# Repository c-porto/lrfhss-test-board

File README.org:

#+HTML: <div align="center">

#+HTML: 
#+HTML: 

* LR-FHSS Test Board 

#+HTML:   </a>
#+HTML:   
#+HTML:   
#+HTML:   
#+HTML:   
#+HTML:   
#+HTML:   <a href="https://doi.org/10.5281/zenodo.19164080"></br>

A simple PCB for testing the LR-FHSS

[[#overview][Overview]] • [[#repository-organization][Repository Organization]] • [[#license][License]] • [[#releases][Releases]] • [[#notes][Notes]] • [[#references][References]]

#+HTML: </div>

* Overview
:PROPERTIES:
:CUSTOM_ID: overview
:END:

The PCB... was based on the on the NiceRF (LoRa1262F30) module...

* Repository Organization
:PROPERTIES:
:CUSTOM_ID: repository-organization
:END:

#+begin_src text  
  lrfhss-test-board/
    ├── README.org
    ├── sources/
    └── outputs/
#+end_src

- =sources/= :: Main files of the... hardware project.
- =outputs/= :: Output files, such as figures of the...PCB, schematics, BOM and more.

* License
:PROPERTIES:
:CUSTOM_ID: license
:END:

This project is open-source under the following license: CERN Open Hardware License v2.0.

* Releases
:PROPERTIES:
:CUSTOM_ID: releases
:END:

Releases are published after ensuring that the project itself does not have any major errors and after testing the PCB. Please refer to the *documentation* for more details.

* Notes
:PROPERTIES:
:CUSTOM_ID: notes
:END:

For more info about the ...

* References
:PROPERTIES:
:CUSTOM_ID: references
:END:

# - <<ref1>> [1] D. L. Figueiredo, "Reliability Enhanced Electrical Power System for Nanosatellites," in /Repositório Institucional da UFSC/, pp. 1-85, 2023, available at [[https://repositorio.ufsc.br/bitstream/handle/123456789/247559/PEEL2103-D.pdf?sequence=1&isAllowed=y][this link]].

# - <<ref2>> [2] C. A. Rigo, L. O. Seman, M. D. Berejuck and E. A. Bezerra, "Printed Circuit Board Design Methodology for Embedded Systems Targeting Space Applications," in /IEEE Latin America Transactions/, vol. 18, no. 02, pp. 257-264, 2020, available at [[https://ieeexplore.ieee.org/document/9085278][this link]].

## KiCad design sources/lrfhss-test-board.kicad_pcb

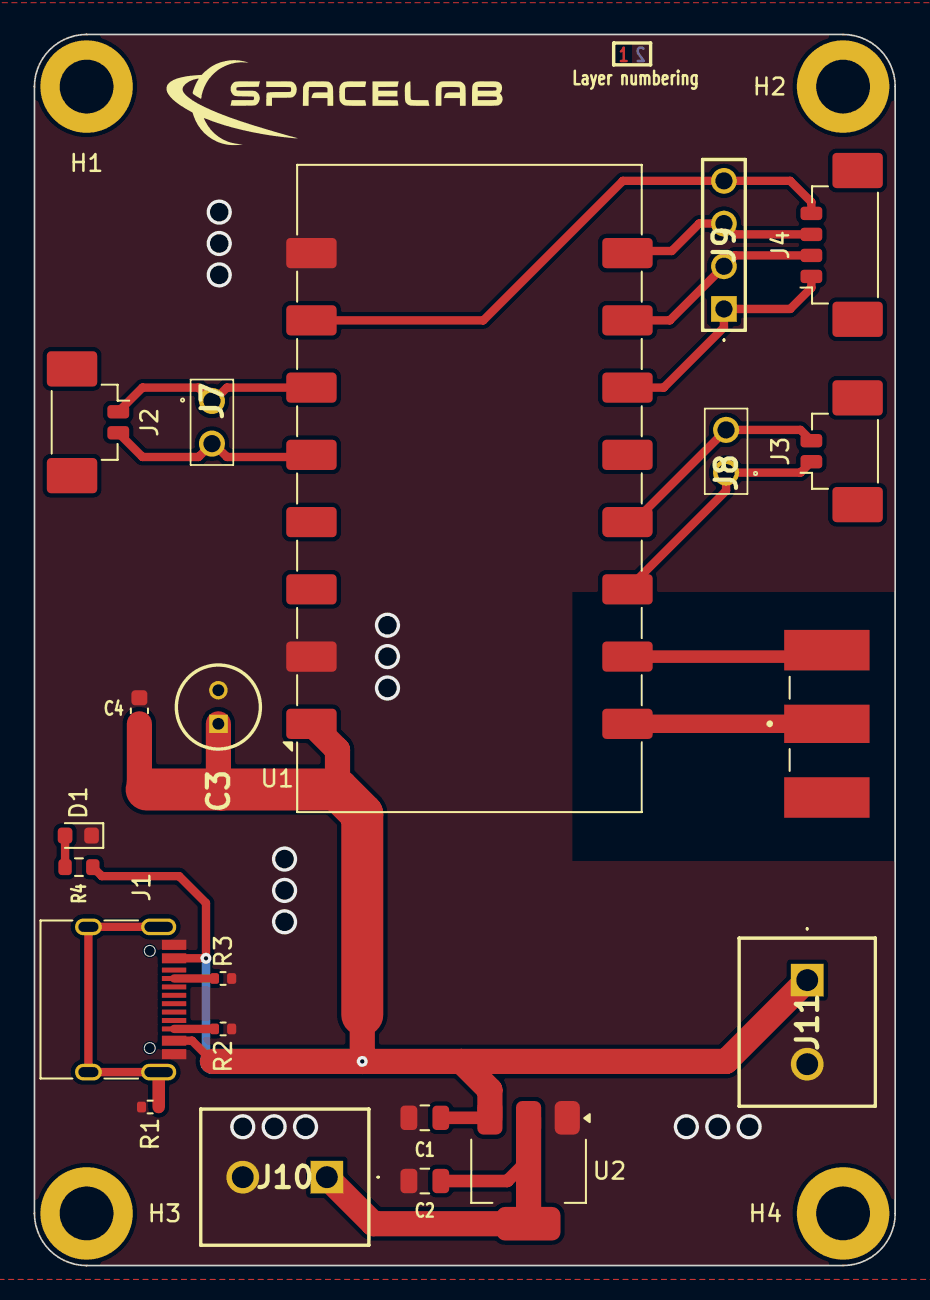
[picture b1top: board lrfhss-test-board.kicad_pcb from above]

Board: 2 copper layers, 51.2 x 73.2 mm, 25 parts (0 on the bottom side), 17 nets.

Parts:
C1, C2: 1uF; CAP0805
C3: 47uF; CAP47UELECTROLYTIC
C4: 100nF; CAP0603
D1: LED; LED_0603_1608Metric
H1, H2, H3, H4: Mounting hole (3.2 mm); MountingHole
J1: USB-C; GENERIC-USB-C
J2, J3: 532610271
J4: 532610471
J5: 142-0701-801
J7, J8: Conn_01x02_Pin; TSW-102-07-G-S
J9: Conn_01x04_Pin; TSW-104-07-G-S
J10, J11: Screw_Terminal_01x02; MV-152
R1: 1M; RES0402
R2, R3: 5.11k; RES0402
R4: 1k; RES0603
U1: LoRa126XF30
U2: AMS1117-3.3; SOT-223-3_TabPin2

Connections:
3V3: C2.2, J10.1, U2.2 (VO)
/CTRL0: J2.2, J7.2, U1.5 (~RESET)
/CTRL1: J2.1, J7.1, U1.6 (BUSY)
/DATA0: J3.1, J8.1, U1.14 (DIO3)
/DATA1: J3.2, J8.2, U1.13 (DIO1)
/SPI0: J4.1, J9.1, U1.11 (MOSI)
/SPI1: J4.2, J9.2, U1.10 (MISO)
/SPI2: J4.3, J9.3, U1.9 (SCK)
/SPI3: J4.4, J9.4, U1.7 (~NSS)
ANT: J5.1, U1.16 (ANT)
GND: C1.1, C2.1, C3.2, C4.1, D1.1 (K), J1.A1 (GND), J1.A12 (GND), J1.B1 (GND), J1.B12 (GND), J10.2, J11.2, R1.1, R2.1, R3.1, U1.2 (GND), U1.8 (GND), U2.1 (GND)
GND1: J5.S1, J5.S2, J5.S3, J5.S4, U1.15 (GND)
unnamed: D1.2 (A), R4.1
unnamed: J1.A5 (CC1), R3.2
unnamed: J1.B5 (CC2), R2.2
unnamed: J1.S1 (SHIELD), R1.2
VBUS: C1.2, C3.1, C4.2, J1.A4 (VBUS), J1.A9 (VBUS), J1.B4 (VBUS), J1.B9 (VBUS), J11.1, R4.2, U1.1 (VCC), U2.3 (VI)

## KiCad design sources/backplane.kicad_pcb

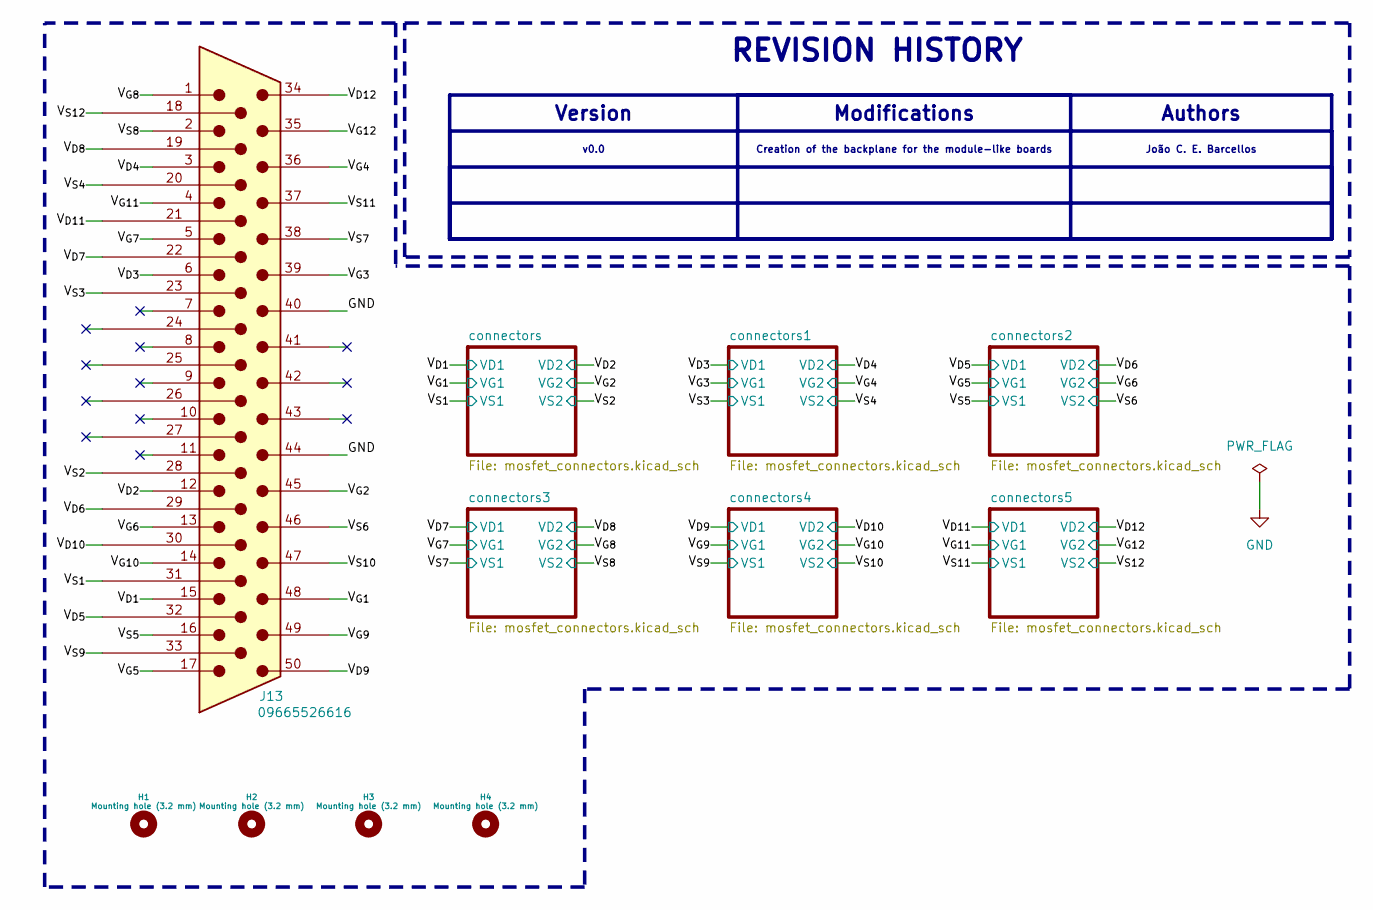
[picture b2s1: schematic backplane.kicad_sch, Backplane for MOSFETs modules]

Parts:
H1, H2, H3, H4: Mounting hole (3.2 mm); MountingHole; MPN N/A
J13: 09665526616; 966552616; Manufacturer_Part_Number 09665526616; Mouser Part Number 617-09-66-552-6616

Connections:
/V_{D1}: J13.15; also elsewhere on the board
/V_{D2}: J13.12; also elsewhere on the board
/V_{D3}: J13.6; also elsewhere on the board
/V_{D4}: J13.3; also elsewhere on the board
/V_{D5}: J13.32; also elsewhere on the board
/V_{D6}: J13.29; also elsewhere on the board
/V_{D7}: J13.22; also elsewhere on the board
/V_{D8}: J13.19; also elsewhere on the board
/V_{D9}: J13.50; also elsewhere on the board
/V_{D10}: J13.30; also elsewhere on the board
/V_{D11}: J13.21; also elsewhere on the board
/V_{D12}: J13.34; also elsewhere on the board
/V_{G1}: J13.48; also elsewhere on the board
/V_{G2}: J13.45; also elsewhere on the board
/V_{G3}: J13.39; also elsewhere on the board
/V_{G4}: J13.36; also elsewhere on the board
/V_{G5}: J13.17; also elsewhere on the board
/V_{G6}: J13.13; also elsewhere on the board
/V_{G7}: J13.5; also elsewhere on the board
/V_{G8}: J13.1; also elsewhere on the board
/V_{G9}: J13.49; also elsewhere on the board
/V_{G10}: J13.14; also elsewhere on the board
/V_{G11}: J13.4; also elsewhere on the board
/V_{G12}: J13.35; also elsewhere on the board
/V_{S1}: J13.31; also elsewhere on the board
/V_{S2}: J13.28; also elsewhere on the board
/V_{S3}: J13.23; also elsewhere on the board
/V_{S4}: J13.20; also elsewhere on the board
/V_{S5}: J13.16; also elsewhere on the board
/V_{S6}: J13.46; also elsewhere on the board
/V_{S7}: J13.38; also elsewhere on the board
/V_{S8}: J13.2; also elsewhere on the board
/V_{S9}: J13.33; also elsewhere on the board
/V_{S10}: J13.47; also elsewhere on the board
/V_{S11}: J13.37; also elsewhere on the board
/V_{S12}: J13.18; also elsewhere on the board
GND: J13.40, J13.44

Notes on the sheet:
João C. E. Barcellos
v0.0
Creation of the backplane for the module-like boards
Version
Modifications
Authors
REVISION HISTORY

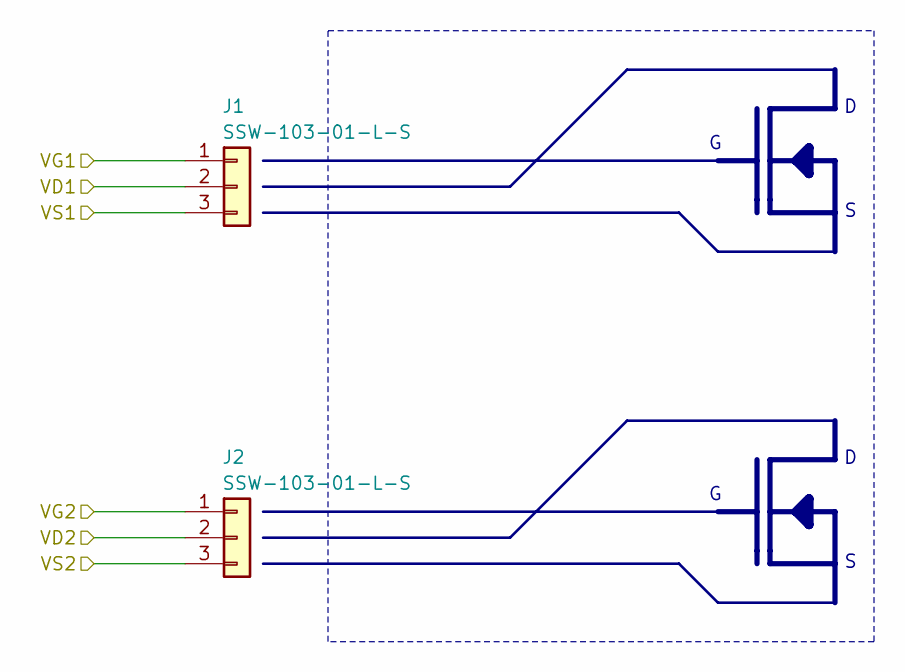
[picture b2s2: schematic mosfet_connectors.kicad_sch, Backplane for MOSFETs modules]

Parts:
J1, J2: SSW-103-01-L-S; MPN SSW-103-01-L-S

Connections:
/V_{D1}: J1.2; also elsewhere on the board
/V_{D2}: J2.2; also elsewhere on the board
/V_{G1}: J1.1; also elsewhere on the board
/V_{G2}: J2.1; also elsewhere on the board
/V_{S1}: J1.3; also elsewhere on the board
/V_{S2}: J2.3; also elsewhere on the board

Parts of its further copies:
J3, J4, J5, J6, J7, J8, J9, J10, J11, J12: SSW-103-01-L-S; MPN SSW-103-01-L-S

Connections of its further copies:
/V_{D3}: J3.2; also elsewhere on the board
/V_{D4}: J4.2; also elsewhere on the board
/V_{D5}: J5.2; also elsewhere on the board
/V_{D6}: J6.2; also elsewhere on the board
/V_{D7}: J7.2; also elsewhere on the board
/V_{D8}: J8.2; also elsewhere on the board
/V_{D9}: J9.2; also elsewhere on the board
/V_{D10}: J10.2; also elsewhere on the board
/V_{D11}: J11.2; also elsewhere on the board
/V_{D12}: J12.2; also elsewhere on the board
/V_{G3}: J3.1; also elsewhere on the board
/V_{G4}: J4.1; also elsewhere on the board
/V_{G5}: J5.1; also elsewhere on the board
/V_{G6}: J6.1; also elsewhere on the board
/V_{G7}: J7.1; also elsewhere on the board
/V_{G8}: J8.1; also elsewhere on the board
/V_{G9}: J9.1; also elsewhere on the board
/V_{G10}: J10.1; also elsewhere on the board
/V_{G11}: J11.1; also elsewhere on the board
/V_{G12}: J12.1; also elsewhere on the board
/V_{S3}: J3.3; also elsewhere on the board
/V_{S4}: J4.3; also elsewhere on the board
/V_{S5}: J5.3; also elsewhere on the board
/V_{S6}: J6.3; also elsewhere on the board
/V_{S7}: J7.3; also elsewhere on the board
/V_{S8}: J8.3; also elsewhere on the board
/V_{S9}: J9.3; also elsewhere on the board
/V_{S10}: J10.3; also elsewhere on the board
/V_{S11}: J11.3; also elsewhere on the board
/V_{S12}: J12.3; also elsewhere on the board

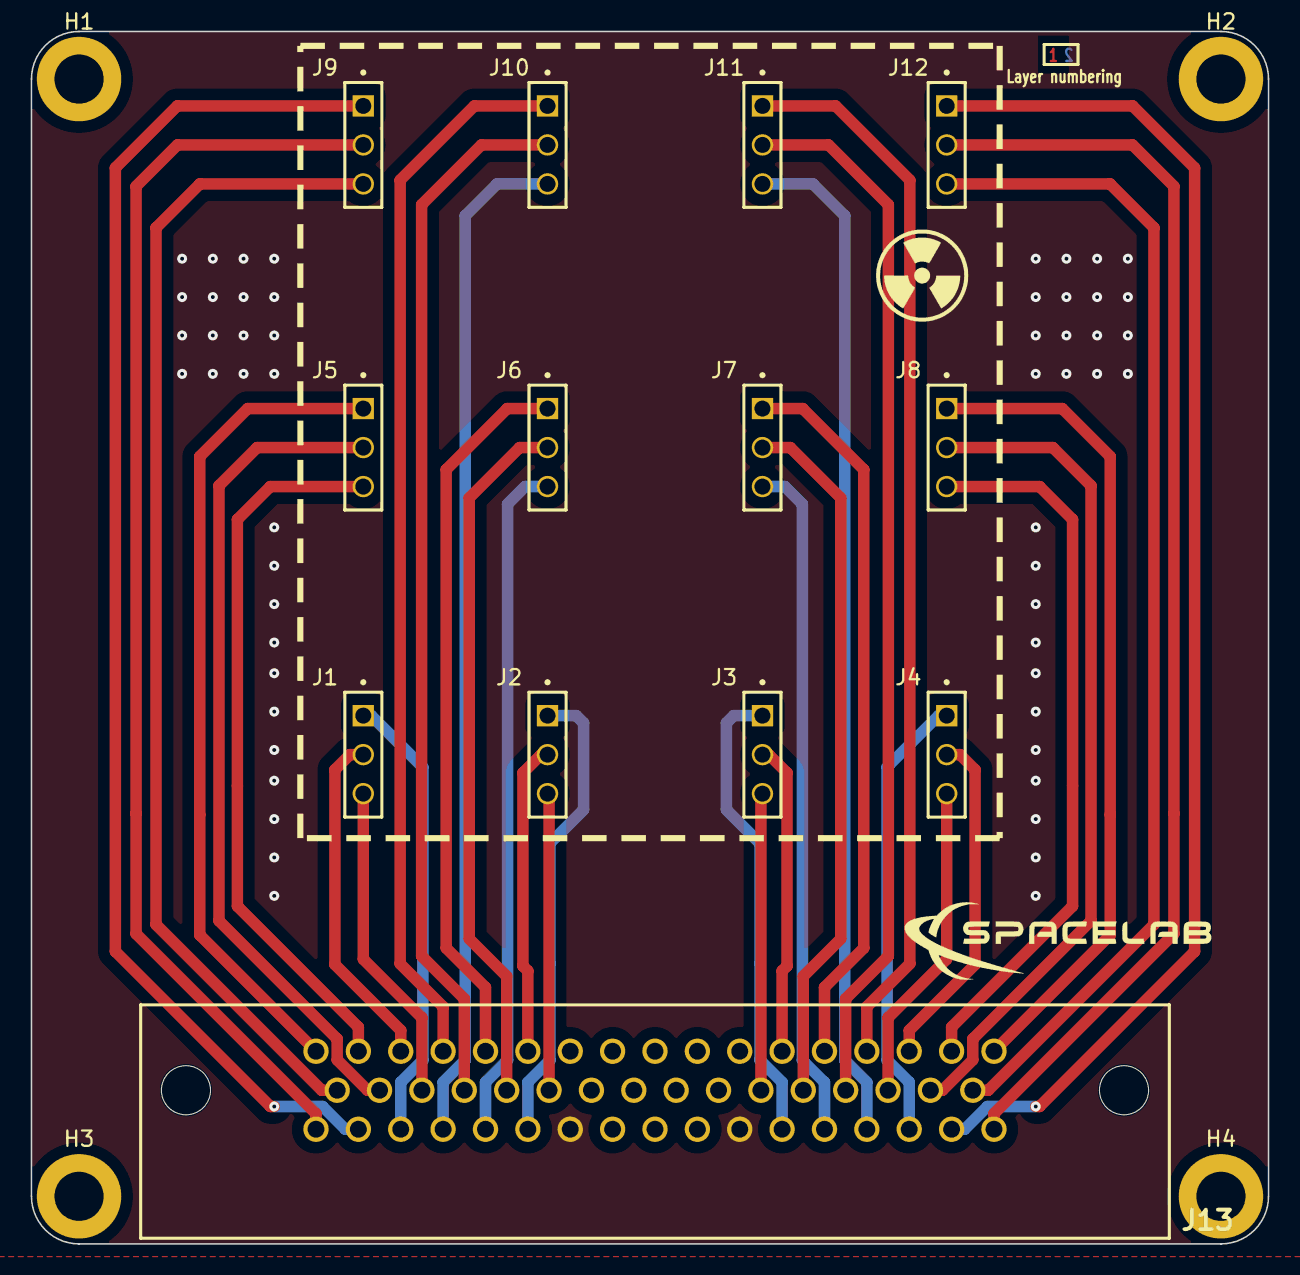
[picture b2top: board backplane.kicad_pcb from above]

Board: 2 copper layers, 80.6 x 79.0 mm, 17 parts (0 on the bottom side), 37 nets.

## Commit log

2026-05-03 Add README
2026-05-06 feat: add the repo. template to start working on the PCB
2026-05-11 feat: add lib folder and minor modifications do the structure
2026-05-27 feat: fix the names of the project files and start adding some symbols
2026-06-05 feat: add initial version of the schematic
2026-06-08 feat: improve schematic and layout
2026-06-08 fix: add 3D model to LoRa module
2026-06-10 fix: add pins to interface with jumpers and some connectors for power
2026-06-11 fix: add final version to fabricate the board at INEP
